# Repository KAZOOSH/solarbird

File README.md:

# Solarbird
Chirping birds with an ATtiny heart.

## How to flash SolarbirdTiny.ino with Arduino IDE

- Get an AVR ISP programmer or a spare Arduino and follow [these instructions](https://create.arduino.cc/projecthub/arjun/programming-attiny85-with-arduino-uno-afb829)
- Under Tools, select board “ATtiny25/45/85”, processor “ATtiny85”, and clock “Internal 8 MHz”
- Again under Tools, click Burn Bootloader (won't actually flash the Arduino bootloader but just set the fuses)
- Optional: change the code to include the bird voice of your choice (see following section)
- Flash the Arduino program as usual by clicking the Upload button

## How to change the bird's voice

At the time of writing, we have an imitation of a blackbird, a chiffchaff, a titmouse and a wren. Check the folder [voices](SolarbirdTiny/voices/) for all available bird voices.

In [SolarbirdTiny.ino near line 23](SolarbirdTiny/SolarbirdTiny.ino#L23), find the lines which include the bird voice and create a _Bird_ instance from it:
```c++
#include "voices/blackbird.h"
Blackbird Bird;
```

Change the name of the included file on the first line to the one of your liking. The code follows the convention that the class name (first word on the second line) is the capitalized version of the filename, i.e., the file `chiffchaff.h` contains the class `Chiffchaff`. After changing both lines, you're ready to upload the new voice to the ATtiny.

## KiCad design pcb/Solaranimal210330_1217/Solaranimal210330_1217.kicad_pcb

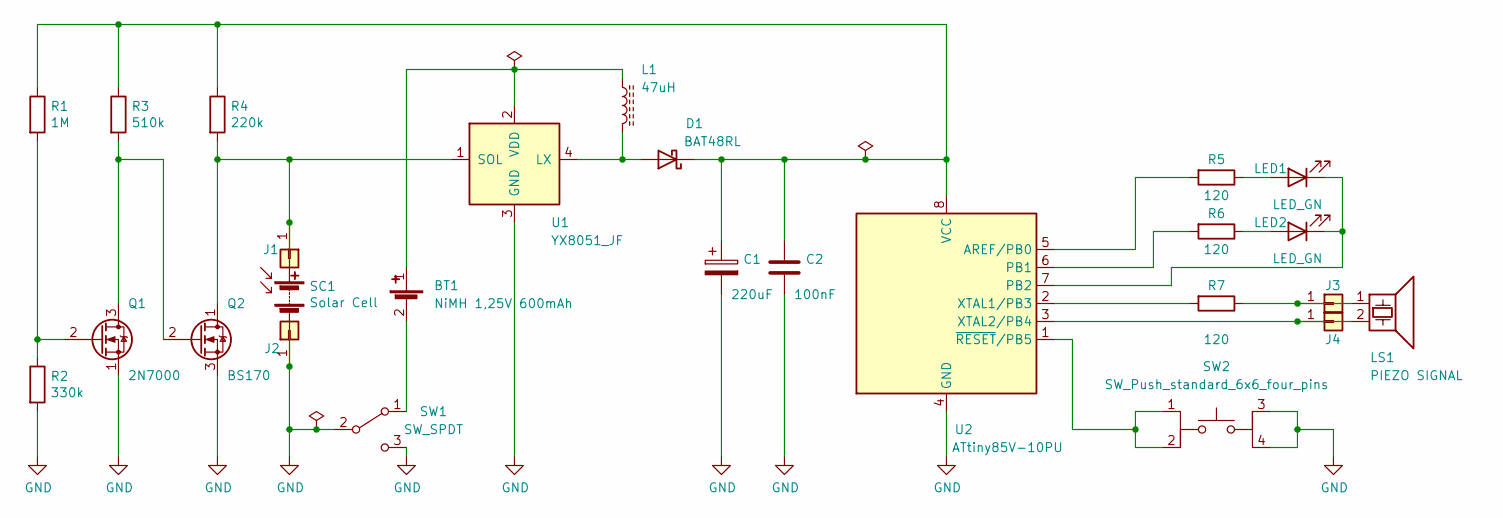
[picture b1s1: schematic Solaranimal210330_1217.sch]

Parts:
BT1: NiMH 1,25V 600mAh; BatteryHolder_Keystone_2466_1xAAA
C1: 220uF; CP_Radial_D6.3mm_P2.50mm
C2: 100nF; C_Disc_D4.7mm_W2.5mm_P5.00mm
D1: BAT48RL; D_DO-35_SOD27_P10.16mm_Horizontal
J1, J2, J3, J4: Conn_01x01; SolderWire-0.5sqmm_1x01_D0.9mm_OD2.1mm_Relief
L1: 47uH; R_Axial_DIN0207_L6.3mm_D2.5mm_P10.16mm_Horizontal
LED1, LED2: LED_GN; LED_D5.0mm
LS1: PIEZO SIGNAL
Q1: 2N7000; TO-92_Inline_Wide
Q2: BS170; TO-92_Inline_Wide
R1: 1M; R_Axial_DIN0207_L6.3mm_D2.5mm_P10.16mm_Horizontal
R2: 330k; R_Axial_DIN0207_L6.3mm_D2.5mm_P10.16mm_Horizontal
R3: 510k; R_Axial_DIN0207_L6.3mm_D2.5mm_P10.16mm_Horizontal
R4: 220k; R_Axial_DIN0207_L6.3mm_D2.5mm_P10.16mm_Horizontal
R5, R6, R7: 120; R_Axial_DIN0207_L6.3mm_D2.5mm_P10.16mm_Horizontal
SC1: Solar Cell
SW1: SW_SPDT; SW_Slide_1P2T_CK_OS102011MS2Q
SW2: SW_Push_standard_6x6_four_pins; SW_PUSH_6mm_H5mm_4pin
U1: YX8051_JF; R_Array_SIP4
U2: ATtiny85V-10PU; DIP-8_W7.62mm

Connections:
GND: C1.2, C2.2, J2.1, Q1.1 (S), Q2.3 (S), R2.2, SC1.2 (-), SW1.2 (B), SW1.3 (C), SW2.3, SW2.4, U1.3 (GND), U2.4 (GND)
unnamed: BT1.1 (-), L1.1, U1.2 (VDD)
unnamed: BT1.2 (plus), SW1.1 (A)
unnamed: C1.1, C2.1, D1.1 (K), R1.1, R3.1, R4.1, U2.8 (VCC)
unnamed: D1.2 (A), L1.2, U1.4 (LX)
unnamed: J1.1, Q2.1 (D), R4.2, SC1.1 (+), U1.1 (SOL)
unnamed: J3.1, LS1.1, R7.1
unnamed: J4.1, LS1.2, U2.3 (XTAL2/PB4)
unnamed: LED1.1 (K), LED2.1 (K), U2.7 (PB2)
unnamed: LED1.2 (A), R5.1
unnamed: LED2.2 (A), R6.1
unnamed: Q1.2 (G), R1.2, R2.1
unnamed: Q1.3 (D), Q2.2 (G), R3.2
unnamed: R5.2, U2.5 (AREF/PB0)
unnamed: R6.2, U2.6 (PB1)
unnamed: R7.2, U2.2 (XTAL1/PB3)
unnamed: SW2.1, SW2.2, U2.1 (~RESET~/PB5)

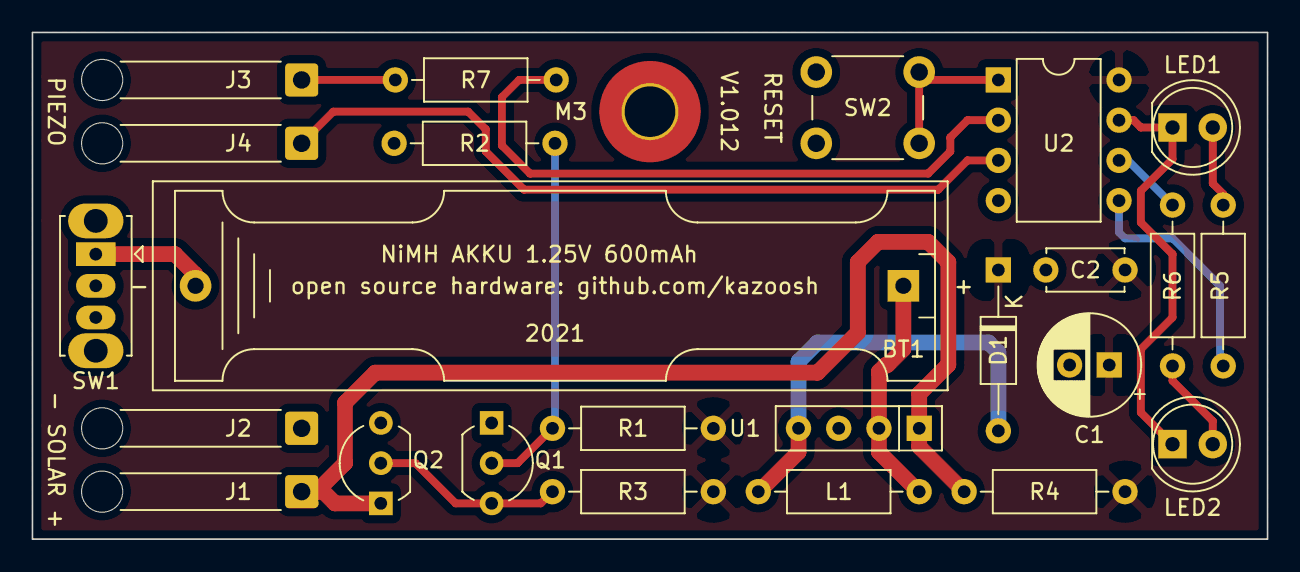
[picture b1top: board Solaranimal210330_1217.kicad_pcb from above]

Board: 2 copper layers, 78.0 x 32.0 mm, 25 parts (0 on the bottom side), 17 nets.

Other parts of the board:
M3: MountingHole_3.2mm_M3_Pad_TopBottom

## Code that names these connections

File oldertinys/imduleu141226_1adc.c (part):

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// (else comment + disable BOD by fuse)

// Pins ATtiny 25,45,85 (13, 13A different INT0-Pin)
#define MOSI 0 //PB0                Pin5 ISP_input
#define MISO 1 //PB1 (t13 INT0)     Pin6 ISP_output
#define SCK 2  //PB2 INT0!          Pin7 ISP_input
#define ADC3 3 //PB3                Pin2 GPIO
#define ADC2 4 //PB4                Pin3 GPIO
//    !RESET   PB5(disabled)        Pin1 RESET
//    VCC                           Pin8
//    GND                           Pin4

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    cli();
    prepareLDR();
    ADCSRA |= (1<<ADEN);                // AD-WANDLER EINSCHALTEN STROMVERBRAUCH 200 MIKROAMPERE
    //ADMUX  = (1<<MUX1);               // ADC2 (PB4, Pin3) INPUT, Vcc as Reference
    ADMUX  = (1<<MUX2)|(1<<MUX1);       // ADC3 (PB3, Pin2) -EINGANG ADC2 (PB4, Pin3) +EINGANG Vcc IST REFERENZWERT
    ADCSRA |= (1<<ADSC);                // dummyconversion 25 ADC-clocks
    while(ADCSRA & (1<<ADSC));          // wait for finishing AD-conversion
   (void) ADCW;                         // ADC-readout to void
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
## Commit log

2021-03-12 add files to material
2021-03-12 update files
2021-03-12 create folder
2021-03-13 add new files
2021-03-13 change files
2021-03-14 add lib files
2021-03-16 upload data cheats
2021-03-16 ade circuits
2021-03-20 add and change file
2021-03-24 load AS7 files from test
2021-03-30 add pcp files
2021-03-30 remove files from pcb
2021-03-30 change pcb to new version
2021-03-30 add .lib files for pcb
2021-03-30 add datasheed to GN LED
2021-03-31 minor changes
2021-04-01 change Q2
2021-04-01 add adc appnotes
2021-04-07 add V1.31 and oshpark and aisler
2021-04-21 new Testversion
2021-04-21 change T85AllTest
2021-04-26 new version with LFSR Noise
2021-04-26 better LFSR PowerMixer
2021-05-02 Add first draft of Arduino program with chirp-based bird voice
2021-05-02 Bugfix
2021-05-02 Add instructions for flashing the Arduino program
2021-05-03 create T85MichisVogel
2021-05-03 Delete test/T85MichisVogel/.vs/T85MichisVogel/v14 directory
    not used
2021-05-09 Add files via upload
    datasheet for toroid cores
    datasheets for yx805
2021-05-09 Integrate LEDs, add deterministic startup test routine
2021-05-09 README: Clarify that flashing instructions refer to using Arduino IDE
2021-05-09 Remove unused header file
2021-05-09 Bugfix: New melody index would not update if actually different than previous
2021-05-09 Blackbird: Shorten long melodies
2021-05-09 Play less melodies, less often
2021-05-09 Increase melody count per play event again
2021-05-09 Blackbird: Shorten melodies further
2021-05-09 Change melodyStartIndex data type in loop() to int for easier reading (will be cast)
2021-05-09 Change delay between melodies of a series from variable to short fixed
2021-05-09 Melody play pattern is bird-specific, hence move to play() method in Blackbird
2021-05-09 Piezo: Replace Atmel toggle hack with ordinary port logic to avoid interference with other pins
2021-05-09 LEDs: Completely avoid digitalWrite, disconnect on switching off
2021-05-09 Move LED flashing on play to Blackbird::playSingleMelody() and make it optional
2021-05-09 Rename io directory to system
2021-05-09 Add author note to Blackbird
2021-05-09 Implement low-power sleep
2021-05-09 LowPower: Add convenient method to sleep multiple seconds, add reference to Atmel documentation
2021-05-09 Better random seed
2021-05-12 Make startup test optional
2021-05-13 add glow LEDs
2021-05-13 rename datasheet
2021-05-16 Softer startup to avoid overloading the fragile power supply
2021-05-16 LEDs: Light refactoring
2021-05-17 LEDs: Add draft of brightness sensing (however unsatisfying, takes too long in darkness)
2021-05-17 LEDs: Improve brightness sensing (limited sensing of dark conditions, better sensitivity in bright conditions)
2021-05-18 Working sketch with brightness-based activity sensing and interactive sound interval
2021-05-18 LEDs: Refactor sensing function and fix bug (complement at the end unnecessary, already counting backwards)
2021-05-18 Move computation of log brightness to leds.h
2021-05-18 Refactor and move brightness query to main loop
2021-05-18 Add night mode with extra long interval between sounds
2021-05-18 Improve random seed once again ;)
2021-05-18 change directory names and add more datasheeds
2021-05-18 add blackbird mp3
2021-05-19 Remain completely silent at night and sense less often to save energy
2021-05-19 LEDs: Sacrifice some accuracy when sensing and avoid disabling interrupts to keep timers running
2021-05-19 LEDs: Make disabling interrupts when sensing a function argument
2021-05-19 Add startup routine to permanently power down when in darkness
2021-05-19 Increase timeout before powering down when starting in darkness
2021-05-19 LowPower: Rename sleepOneSecond to sleepSecond to be more consistent with sleepSeconds
2021-05-19 Blackbird: Add source of original bird voice recording
2021-05-19 add spice simulation
2021-05-19 fix spice simulation
2021-05-22 add dynamic loads
2021-05-23 add capsense solution
2021-05-24 add erroramp simulation
2021-05-31 add circuit folder
2021-06-02 Chiffchaff: Implement first melodies
2021-06-02 Chiffchaff: Better melody slicing for more variety
2021-06-02 Improved power supply allows to disable power down on startup and to decrease sleep interval in darkness
2021-06-02 Titmouse: A new simple bird :)
2021-06-02 change circuit
2021-06-02 remove backup files
2021-06-07 change Rs (better match with our pool)
2021-06-09 Create Solarvogel
2021-06-09 Make silence at night optional
2021-06-28 Extend piezo chirp function to support different tone period update intervals - needed for slow chirps at high frequencies - also disable interrupts by default to avoid glitches in tone generation
2021-06-28 Wren: First draft of new bird melodies
2021-06-30 Readme: more detailed instructions on flashing, info on how to change the bird's voice
2021-06-30 Put choice of bird voice closer to top in SolarbirdTiny.ino
2021-06-30 Readme: correct line number
2021-07-01 create Vogelnahmen.txt and delete older names
2021-07-21 Roughly compensate CPU delay in piezo tone function
2021-07-21 Wedding mode
2021-08-11 create debugserial
2021-08-12 debugging
2021-08-15 change file structure
